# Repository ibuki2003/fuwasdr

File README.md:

# fuwasdr

wideband receiver from scratch

## memory mapping

- 0x10000000 (2M): FLASH
  - 0x0..0x1cc000: program text
  - 0x1cc000..0x1ce000 (8k): large font
  - 0x1ce000..0x200000 (200k): misaki font

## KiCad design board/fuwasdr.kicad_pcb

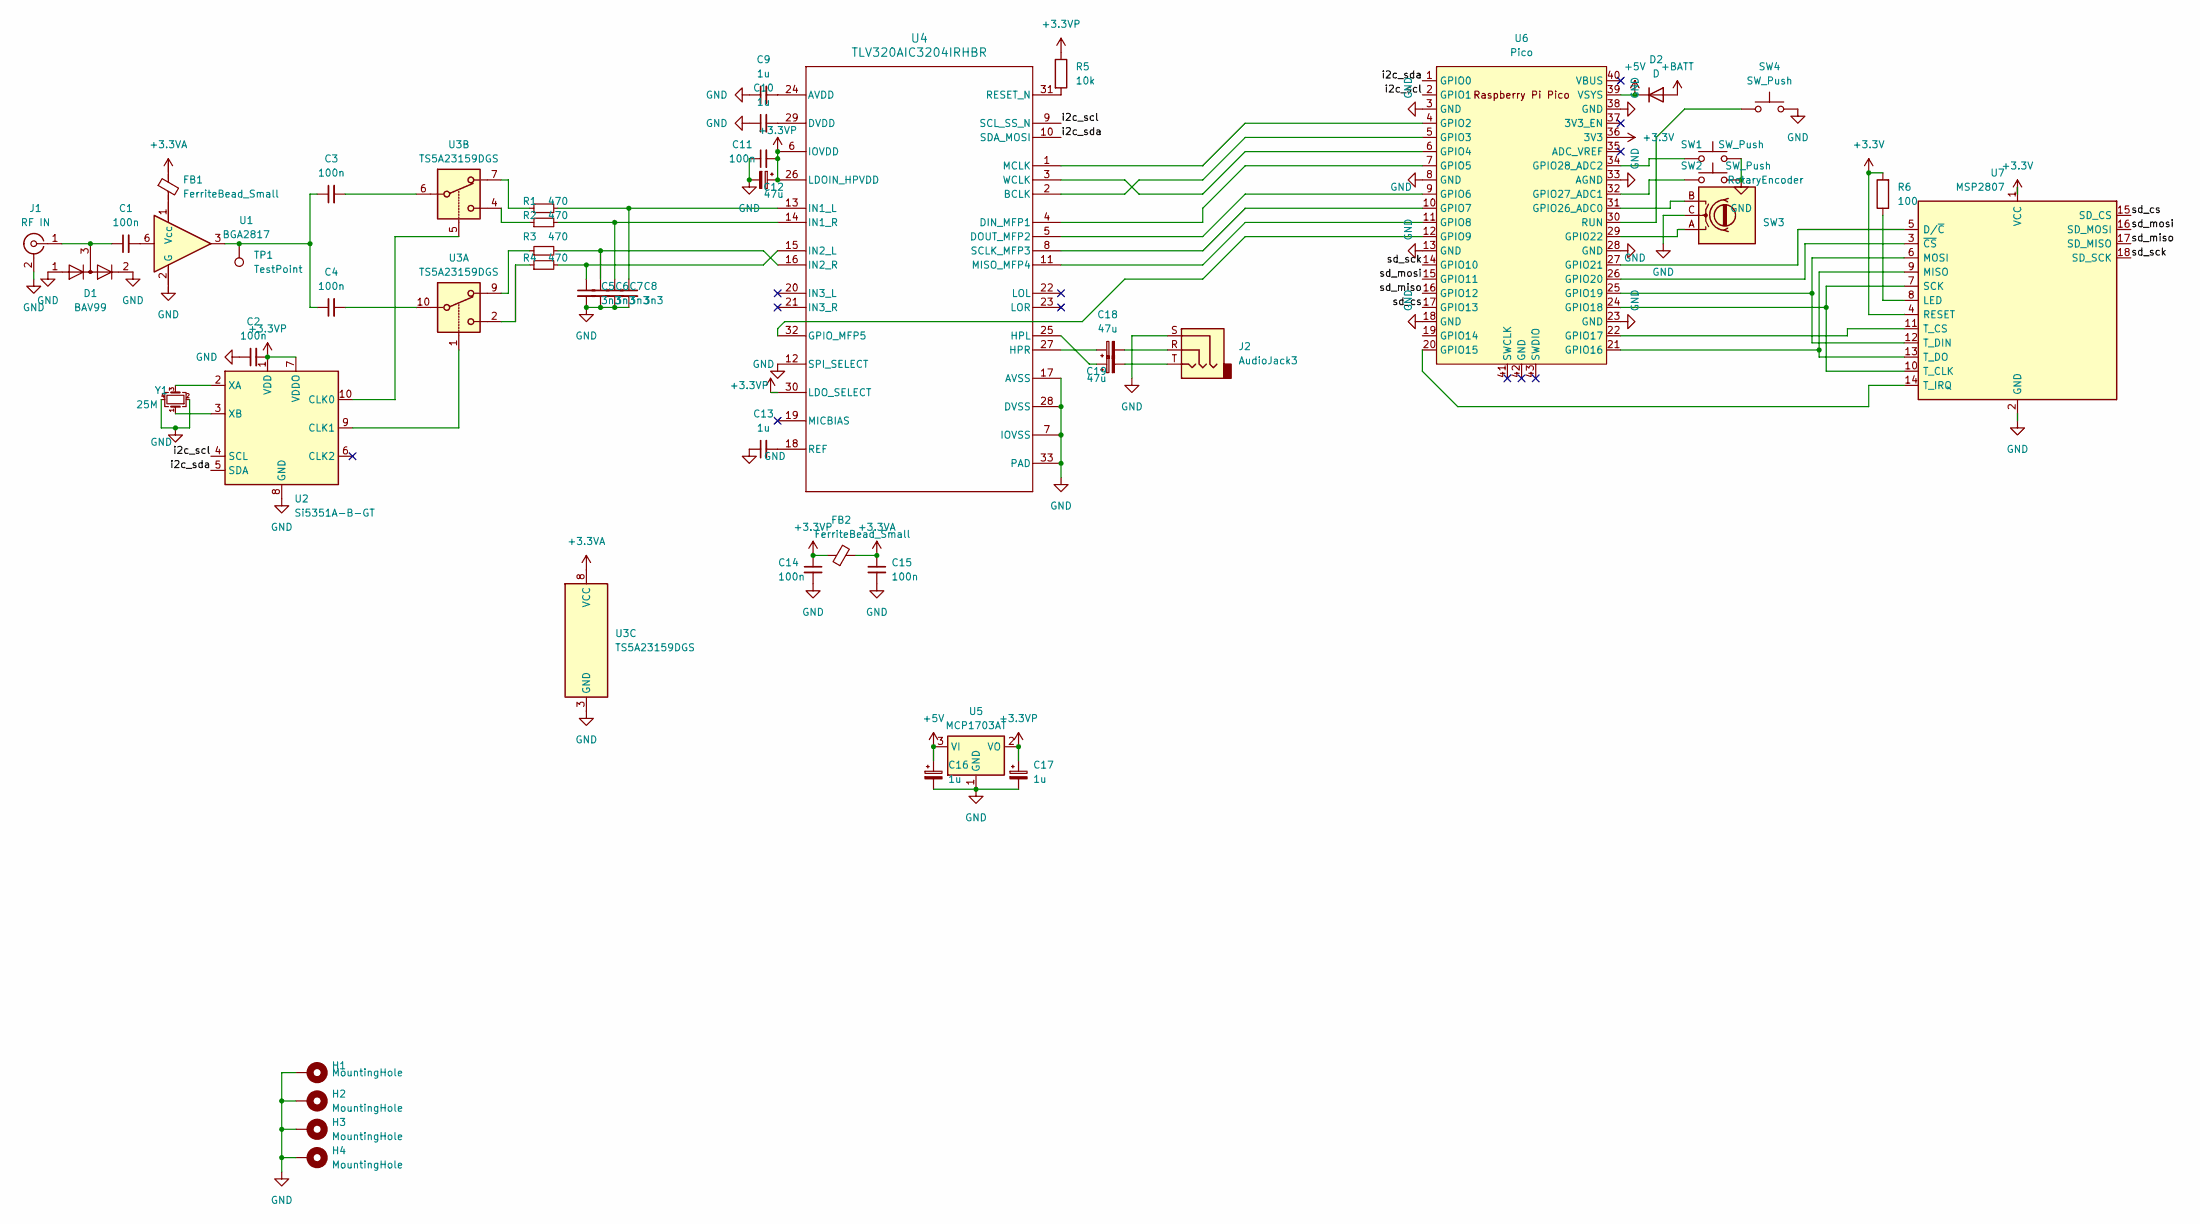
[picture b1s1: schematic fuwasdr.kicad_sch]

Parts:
C1, C2, C3, C4, C11, C14, C15: 100n; C_0603_1608Metric_Pad1.08x0.95mm_HandSolder
C5, C6, C7, C8: 3n3; C_0603_1608Metric_Pad1.08x0.95mm_HandSolder
C9, C10, C13: 1u; C_0603_1608Metric_Pad1.08x0.95mm_HandSolder
C12: 47u; CP_Radial_D5.0mm_P2.00mm
C16, C17: 1u; CP_Radial_D5.0mm_P2.00mm
C18, C19: 47u; CP_Radial_D6.3mm_P2.50mm
D1: BAV99; SOT-23
D2: D; D_SMA
FB1, FB2: FerriteBead_Small; L_0603_1608Metric_Pad1.05x0.95mm_HandSolder
H1, H2, H3, H4: MountingHole; MountingHole_3.2mm_M3_Pad
J1: RF IN; SMA_Amphenol_901-143_Horizontal
J2: AudioJack3; Jack_3.5mm_Switronic_ST-005-G_horizontal
R1, R2, R3, R4: 470; R_0603_1608Metric_Pad0.98x0.95mm_HandSolder
R5: 10k; R_0603_1608Metric_Pad0.98x0.95mm_HandSolder
R6: 100; R_0603_1608Metric_Pad0.98x0.95mm_HandSolder
SW1, SW2: SW_Push; SW_PUSH_6mm
SW3: RotaryEncoder; RotaryEncoder_Alps_EC12E_Vertical_H20mm
SW4: SW_Push; SW_Push_1P1T_NO_Vertical_Wuerth_434133025816
TP1: TestPoint; TestPoint_Pad_D1.5mm
U1: BGA2817; SOT-363_SC-70-6
U2: Si5351A-B-GT; MSOP-10_3x3mm_P0.5mm
U3: TS5A23159DGS; VSSOP-10_3x3mm_P0.5mm
U4: TLV320AIC3204IRHBR; Texas_S-PVQFN-N32_EP3.45x3.45mm
U5: MCP1703AT; SOT-23
U6: Pico; RPi_Pico_SMD_TH_changed_smd
U7: MSP2807; MSP2807_floating
Y1: 25M; Crystal_SMD_2016-4Pin_2.0x1.6mm

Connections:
+3.3V: R6.2, U6.36 (3V3), U7.1 (VCC), U7.4 (RESET)
+3.3VA: C15.1, FB1.1, FB2.2, U3.8 (VCC)
+3.3VP: C2.2, C11.2, C12.1, C14.1, C17.1, FB2.1, R5.1, U2.1 (VDD), U2.7 (VDDO), U4.6 (IOVDD), U4.26 (LDOIN_HPVDD), U4.30 (LDO_SELECT), U5.2 (VO)
+5V: C16.1, D2.1 (K), U5.3 (VI), U6.39 (VSYS)
+BATT: D2.2 (A)
/i2c_scl: U2.4 (SCL), U4.9 (SCL_SS_N), U6.2 (GPIO1)
/i2c_sda: U2.5 (SDA), U4.10 (SDA_MOSI), U6.1 (GPIO0)
/sd_cs: U6.17 (GPIO13), U7.15 (SD_CS)
/sd_miso: U6.16 (GPIO12), U7.17 (SD_MISO)
/sd_mosi: U6.15 (GPIO11), U7.16 (SD_MOSI)
/sd_sck: U6.14 (GPIO10), U7.18 (SD_SCK)
GND: C2.1, C5.2, C6.2, C7.2, C8.2, C9.1, C10.1, C11.1, C12.2, C13.1, C14.2, C15.2, C16.2, C17.2, D1.1 (K), D1.2 (A), H1.1, H2.1, H3.1, H4.1, J1.2 (Ext), J2.S, SW1.2, SW2.2, SW3.C, SW4.2, U1.2 (G), U1.4 (G), U1.5 (G), U2.8 (GND), U3.3 (GND), U4.7 (IOVSS), U4.12 (SPI_SELECT), U4.17 (AVSS), U4.28 (DVSS), U4.33 (PAD), U5.1 (GND), U6.3 (GND), U6.8 (GND), U6.13 (GND), U6.18 (GND), U6.23 (GND), U6.28 (GND), U6.33 (AGND), U6.38 (GND), U7.2 (GND), Y1.2, Y1.4
unnamed: C1.2, U1.6
unnamed: C3.1, C4.1, TP1.1, U1.3
unnamed: C3.2, U3.6
unnamed: C4.2, U3.10
unnamed: C18.2, J2.R
unnamed: C19.2, J2.T
unnamed: C1.1, D1.3 (K), J1.1 (In)
unnamed: R1.1, U3.7
unnamed: R2.1, U3.4
unnamed: R3.1, U3.9
unnamed: R4.1, U3.2
unnamed: FB1.2, U1.1 (Vcc)
unnamed: U2.10 (CLK0), U3.5
unnamed: U2.9 (CLK1), U3.1
unnamed: U2.2 (XA), Y1.3
unnamed: U2.3 (XB), Y1.1
unnamed: C9.2, U4.24 (AVDD)
unnamed: U4.2 (BCLK), U6.5 (GPIO3)
unnamed: U4.4 (DIN_MFP1), U6.7 (GPIO5)
unnamed: U4.5 (DOUT_MFP2), U6.9 (GPIO6)
unnamed: C10.2, U4.29 (DVDD)
unnamed: U4.32 (GPIO_MFP5), U6.12 (GPIO9)
unnamed: C19.1, U4.25 (HPL)
unnamed: C18.1, U4.27 (HPR)
unnamed: C8.1, R1.2, U4.13 (IN1_L)
unnamed: C7.1, R2.2, U4.14 (IN1_R)
unnamed: C5.1, R4.2, U4.15 (IN2_L)
unnamed: C6.1, R3.2, U4.16 (IN2_R)
unnamed: U4.1 (MCLK), U6.4 (GPIO2)
unnamed: U4.11 (MISO_MFP4), U6.11 (GPIO8)
unnamed: C13.2, U4.18 (REF)
unnamed: R5.2, U4.31 (RESET_N)
unnamed: U4.8 (SCLK_MFP3), U6.10 (GPIO7)
unnamed: U4.3 (WCLK), U6.6 (GPIO4)
unnamed: U6.20 (GPIO15), U7.14 (T_IRQ)
unnamed: U6.21 (GPIO16), U7.9 (MISO), U7.13 (T_DO)
unnamed: U6.22 (GPIO17), U7.11 (T_CS)
unnamed: U6.24 (GPIO18), U7.7 (SCK), U7.10 (T_CLK)
unnamed: U6.25 (GPIO19), U7.6 (MOSI), U7.12 (T_DIN)
unnamed: U6.26 (GPIO20), U7.3 (~CS)
unnamed: U6.27 (GPIO21), U7.5 (D/~C)
unnamed: SW3.A, U6.29 (GPIO22)
unnamed: SW3.B, U6.31 (GPIO26_ADC0)
unnamed: SW2.1, U6.32 (GPIO27_ADC1)
unnamed: SW1.1, U6.34 (GPIO28_ADC2)
unnamed: SW4.1, U6.30 (RUN)
unnamed: R6.1, U7.8 (LED)

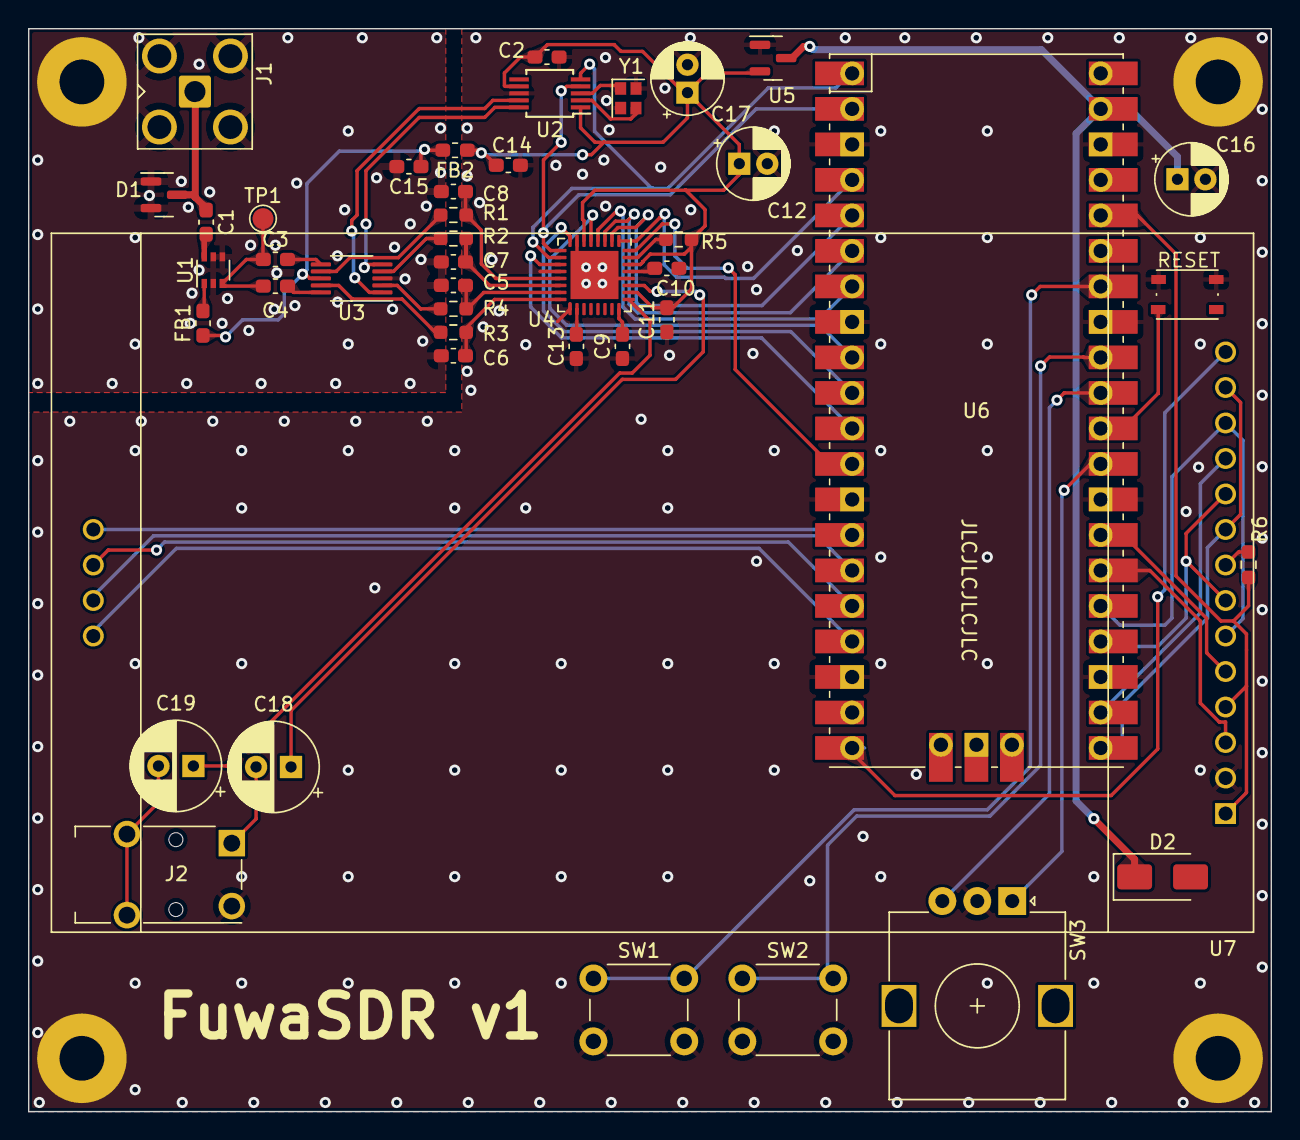
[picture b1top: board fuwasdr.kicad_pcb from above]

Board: 2 copper layers, 88.9 x 77.5 mm, 48 parts (0 on the bottom side), 58 nets.

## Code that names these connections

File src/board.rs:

use crate::hal;

hal::bsp_pins! {
    Gpio0  { name: i2c_sda, aliases: { FunctionI2c, PullUp: PinI2cSda  } },
    Gpio1  { name: i2c_scl, aliases: { FunctionI2c, PullUp: PinI2cScl } },

    Gpio2  { name: codec_mclk, aliases: { FunctionPio0, PullUp: PinCodecMclk   } },
    Gpio3  { name: codec_bclk, aliases: { FunctionPio0, PullUp: PinCodecBclk   } },
    Gpio4  { name: codec_wclk, aliases: { FunctionPio0, PullUp: PinCodecWclk   } },
    Gpio5  { name: codec_mfp1, aliases: { FunctionPio0, PullUp: PinCodecMfp1   } },
    Gpio6  { name: codec_mfp2, aliases: { FunctionPio0, PullUp: PinCodecMfp2   } },
    Gpio7  { name: codec_mfp3, aliases: { FunctionNull, PullNone: PinCodecMfp3 } },
    Gpio8  { name: codec_mfp4, aliases: { FunctionNull, PullNone: PinCodecMfp4 } },
    Gpio9  { name: codec_mfp5, aliases: { FunctionNull, PullNone: PinCodecMfp5 } },

    Gpio10 { name: sd_sck,  aliases: { FunctionNull, PullNone: PinSdSck  } },
    Gpio11 { name: sd_mosi, aliases: { FunctionNull, PullNone: PinSdMosi } },
    Gpio12 { name: sd_miso, aliases: { FunctionNull, PullNone: PinSdMiso } },
    Gpio13 { name: sd_cs,  aliases: { FunctionNull, PullNone: PinSdCs   } },

    Gpio14 { name: lcd_reset,    aliases: { FunctionSioOutput, PullUp: PinLcdReset    } },
    Gpio16 { name: lcd_miso,     aliases: { FunctionSpi,       PullUp: PinLcdMiso     } },
    Gpio18 { name: lcd_sck,      aliases: { FunctionSpi,       PullUp: PinLcdSck      } },
    Gpio19 { name: lcd_mosi,     aliases: { FunctionSpi,       PullUp: PinLcdMosi     } },
    Gpio15 { name: lcd_touchirq, aliases: { FunctionSioInput,  PullUp: PinLcdTouchIrq } },
    Gpio17 { name: lcd_touchcs,  aliases: { FunctionSioOutput, PullUp: PinLcdTouchCs  } },
    Gpio20 { name: lcd_dispcs,   aliases: { FunctionSioOutput, PullUp: PinLcdDispCs   } },
    Gpio21 { name: lcd_dcrs,     aliases: { FunctionSioOutput, PullUp: PinLcdDcRs     } },

    Gpio22 { name: rotary_a, aliases: { FunctionSioInput, PullUp: PinRotaryA } },
    Gpio26 { name: rotary_b, aliases: { FunctionSioInput, PullUp: PinRotaryB } },

    Gpio23 { name: bpowersave, aliases: { FunctionNull, PullNone: BPowerSave     } },
    Gpio24 { name: vbus, aliases: { FunctionNull, PullNone: VBusDetect     } },
    Gpio25 { name: led, aliases: { FunctionSioOutput, PullNone: OnBoardLed     } },

    Gpio27 { name: button_2, aliases: { FunctionSioInput, PullUp: PinButton2     } },
    Gpio28 { name: button_1, aliases: { FunctionSioInput, PullUp: PinButton1     } },
}

pub type I2CDevice = hal::pac::I2C0;
pub type I2C = hal::i2c::I2C<I2CDevice, (PinI2cSda, PinI2cScl)>;
pub type LcdSpiDevice = hal::pac::SPI0;

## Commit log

2024-02-05 build: setup rp2040
2024-02-05 build: embedded-hal 1.0.0
2024-02-05 feat: number structs
2024-02-06 feat: math utils
2024-02-07 feat: board pins
2024-02-09 feat: codec lib
2024-02-10 feat: add Si5351a controller
2024-02-10 build: increase optimize level for debug
2024-02-10 feat: split into core module
2024-02-10 format: cargo fmt
2024-02-10 refactor: rename module pins to board
2024-02-10 build: add dependency critical_section
2024-02-12 feat: use static shared i2c bus
2024-02-12 fix: clockgen tuning
2024-02-13 fix: codec manipulation
2024-02-13 feat: quadrature at lower freq
2024-02-13 build: usb-device and usbd-audio
2024-02-13 feat: lcd reset for pin 14
2024-02-14 feat: rotary encoder input
2024-02-15 fix: quadrature phase swap
2024-02-15 feat: add codec methods
2024-02-15 feat: fft
2024-02-15 feat: LCD control
2024-02-16 feat: SDR works over usb audio
2024-02-17 fix: FFT calculatiion
2024-02-17 refactor: use bsp_pins! for pin type manage
2024-02-17 fix: add display module
2024-02-18 feat: button controll
2024-02-18 build: enable lto on debug build
2024-02-18 refactor: cleanup code
2024-02-19 feat: use DMA
2024-02-19 feat: add codec hysteresis
2024-02-27 feat: interrupt approach
2024-02-27 feat: DSPNum Default derive
2024-02-28 chore: add board
2024-02-28 feat: manual gain control
2024-03-11 feat: text rendering font selection support
2024-03-11 refactor: use auto increment on codec setup
2024-03-11 feat: adc DC cut
2024-03-11 style: auto format
2024-03-11 feat: show freq on waterfall
2024-03-11 feat: show subgrid on waterfall frequency
2024-03-27 fix: i2s output
2024-03-27 feat: demodulation
2024-03-27 feat: demodulation freq tune
2024-03-27 feat: tune and volume control
2024-03-27 fix: remove unused import
2024-03-27 feat: improve volume control
2024-03-27 feat: fm demodulation
2024-03-30 chore: panic halt
2024-03-30 feat: misaki text rendering
2024-03-30 doc: add font generating documentations
2024-03-30 refactor: move display manager to core
2024-08-27 feat: waterfall logarighmic scale
